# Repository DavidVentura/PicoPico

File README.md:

# Pico Pico

Project to attempt to create hardware for the [Pico-8](https://www.lexaloffle.com/pico-8.php).

I'd like to eventually get full game running on a ~[Raspberry Pi Pico](https://www.raspberrypi.com/documentation/microcontrollers/raspberry-pi-pico.html)~ [ESP32](https://www.adafruit.com/product/3979)

Be aware, the code will be terrible, this is a project to learn:

* C
* SDL
* Embedded
* CMake
* Lua
    * And how to adapt / modify languages
* JIT-ting ??

This project uses [z8lua](https://github.com/DavidVentura/z8lua) to implement Pico8's Lua dialect; I've whacked the original repo to make it build 
with the Pico as a target, it was all implicit casting, which I hopefully got right.

This project also gets some "inspiration" from [tac08](https://github.com/0xcafed00d/tac08/tree/master/src) - ideas for things I don't know how to solve, and the "firmware.lua" file 
for basic implementations.

## Demo

### In emulator (SDL/rawdraw backed)

https://user-images.githubusercontent.com/3650670/209883786-df8e24eb-6469-4147-87f5-97d2407c08f9.mp4

### Celeste in ESP32

https://user-images.githubusercontent.com/3650670/168416377-bf238d62-6be6-4b70-a04c-2d60ab57a269.mp4

### In Raspberry pi Pico (port abandoned, not enough RAM)

https://user-images.githubusercontent.com/3650670/166146124-06b8b223-27b1-47ac-931f-67ba8b523d9e.mp4

### On Android

https://github.com/DavidVentura/PicoPico/assets/3650670/8b1ce7c6-c577-427d-8bed-b0ab688078c9

### On 3DS

https://github.com/DavidVentura/PicoPico/assets/3650670/648f5ae0-5fe0-4eac-8bdf-cbaad8db8e8a

## Hardware

### BOM

* 1x THT Power switch [TME](https://www.tme.eu/nl/en/details/os102011ma1qn1/slide-switches/c-k/) [PDF](https://www.tme.eu/Document/b47a7178f6dd5c46f052ff087f56764e/OS_series_DTE.pdf)
* 8x SMD button [TME](https://www.tme.eu/nl/en/details/evqq2202w/microswitches-tact/panasonic/) [PDF](https://www.tme.eu/Document/7162409d248aba412c7389d402f46025/EVQQ2series.pdf)
* 1x 10k horixontal potentiometer [TME](https://www.tme.eu/nl/en/details/r0141-2-10k/single-turn-tht-trimmers/sr-passives/) [PDF](https://www.tme.eu/Document/48eb4fb11c5e0c9b1cd467745dfbcb98/R0141-2.pdf)
* 8x SMD 10k resistor
* MAX98357 I2S audio amplifier [ALI](https://www.aliexpress.com/item/1005004280540810.html?spm=a2g0o.order_list.order_list_main.11.5b1c18020Z9uMr)
* ESP32 "Wrover" with 4MB PSRAM [Amazon](https://www.amazon.de/gp/product/B07RWHK65X/ref=ppx_yo_dt_b_asin_title_o08_s00?ie=UTF8&psc=1)
* 1.77" SPI ST7735 128x160 Display (128x128 used for game, 16px for UI, 16px padding) [ALI](https://www.aliexpress.com/item/1005003797803015.html?spm=a2g0o.order_list.order_list_main.23.5b1c18020Z9uMr)

# Goals

1. ✅ Make `hello_world` work without regressions )).
    * ~All letters are white~ (lazy palette evaluation was missing a palette indirection (screen vs draw))
1. ✅ Make `rockets` fully playable (without music // complete SFX).
    * ~Points go up too fast~ (`time()` was returning millis)
1. ✅ Create some basic automated testing.
    * Tests are at `tests/`, they run one (or a few) frames and get output.
    * Need to integrate better into the project; exclusive `ifdef` for header selection
1. Make `celeste` fully playable (without music // complete SFX)
    * ~Clouds suddenly appear~ (bad rectfill types, took uint instead of int)
    * Sometimes 2 celestes appear?? mostly on level crossings
1. Make `valdi` fully playable (without music // complete SFX)
    * ~Renders offset when looking to the left~ (wasn't calculating the sprite width accordingly in `spr()`)
    * `fillp` not implemented (background)
    * ~Super slow after a few resets?~ (`gfx_line` was missing a bounds check, overwriting the delay between frames)
1. Make `awake` fully playable (without music // complete SFX)
    * Colors are super glitched, level2 is also glitched

# Basic analysis / feasibility:

Memory requirements:

* Spritesheet, at 128x128 in size = 16KB 
    * Can move to flash
* Fontsheet, at 128x128 in size = 16KB
    * Can move to flash
* Map, at 64x128 = 8 KB
    * Can move to flash
* Flags, at 2x128 = 256B
    * Can move to flash
* Sound effects, 64x84 = 5376B (~5KB)
    * Can move to flash
* Music patterns, 64x6 = 384B
    * Can move to flash
* Front buffer 128x128/2 = 8KB (x/y position -> palette)
* Back buffer 128x128x2 = 32KB (x/y position -> color, at 16bpp)
* HUD buffer 16x128x2 = 4KB
    * Can squeeze to 8x64x2 = 1KB, or even 7 sprites (896b)
* Dedicated "Game memory" = 32KB

Totals ~130KB (of which 76KB for screen buffers and game memory have to stay).

And **most importantly** 2MB for game RAM (Lua memory). This varies based on each game, but on the PICO the 264KB ran out pretty fast. There's [this thing](https://github.com/yocto-8/yocto-8/blob/main/doc/extmem.md) to use _very slow, very cursed_ external RAM. _Some_ games 

# Performance

In RPI Pico:

Running `hello_world.lua`:

* Normal: 13ms / frame; of which:
    * Lua: ~9ms / frame
    * Copying backbuffer to screen (`uint8_t`): ~4ms / frame

* Display on 2nd core: 7.5ms / frame; of which:
    * Lua: ~7ms / frame
    * ~Copying backbuffer to screen~ happens "for free" in the other core

* Multicore + overclock to 260MHz: 3.5ms/frame

In ESP32:

Celeste takes about 9ms / frame (rendering happens on the second core), including SFX

# TODO

Immediate:

* ~Get basic rendering on the Pico~
    * ~split backends properly~
* ~Read code from p8 file instead of having split files~
* ~Implement map~
* ~Implement camera~
* ~Lua dialect~ (using z8lua)
* ~Unify the build systems (Make for pc / CMake for pico)~
* ~Pre-encode the palette colors as a RGB565 `uint16_t`; makes no sense to shift them on _every pixel write_~
* ~SFX~
* ~Measure and output the correct number of samples out of the audio buffer, currently it's a (badly) guessed number.~
* ~Get reasonable audio quality out of SFX~
* Deal with warnings when building for ESP
    * ~Figure out why they don't show up when building with SDL backend~
* ~Move hardcoded pin for ESP32 to sdkconfig~
    * Extract current values for docs WIP
* Implement more complete SFX
* Generate board captures automatically
* ~Add support for short-hand print ('?"x"' == print("x"))~
* Implement fillp https://pico-8.fandom.com/wiki/Fillp
* Lua error: bad argument #1 to 'split' (string expected, got nil)
* Lua error: bad argument #1 to 'btn' (number expected, got nil)
    * z8lua considers literal circle (🅾️) to be `nil` but not ❎

Later:

* ~Clock rate on SPI?~ set to 62.5MHz; not sure if it can go higher
* Implement flash
    * cartdata command could use it
    * carts could be stored in flash instead of static data
* Investigate pushing pixels to display via DMA
    * worth it? the second core is idle anyway
* Music
* Look at optimizing lua bytecode for "fast function calls", for "standard library"
* Use headers instead of stupid ifdefs
* Enable `-Wconversion`
* Console-based UI game
    * [Virtual keyboard](https://www.lexaloffle.com/bbs/?tid=41855) [(original, no lowercase)](https://www.lexaloffle.com/bbs/?tid=4076)
    * Wifi menu
    * Cart explorer?

# Other stuff

Resources are parsed from plaintext into a header by the `to_c.py` script, this also covers converting source code to byte-code. 
Having byte-code compiled in a pre-processing stage makes parsing faster (112ms -> 18ms for a large cart), uses less memory (bytecode 
stays in flash, not necessary to load to RAM) and enables future bytecode-level optimization

## Sound

I yoinked [zepto8's synth](https://github.com/samhocevar/zepto8/blob/master/src/synth.cpp) and converted it to `fix32`; an example SFX went 
from ~25ms to ~2ms on the ESP32.

# API Support

## Graphics

|    Function   | Supported |                     Notes |
|---------------|-----------|---------------------------|
|camera         |✅         |                           |
|circ           |✅         |                           |
|circfill       |✅         |                           |
|oval           |✅         |                           |
|ovalfill       |✅         |                           |
|clip           |✅         |                           |
|cls            |✅         |                           |
|color          |✅         |                           |
|cursor         |❌         |                           |
|fget           |✅         |                           |
|fillp          |❌         |                           |
|fset           |❌         |                           |
|line           |✅         |                           |
|pal            |⚠️          |Only "draw palette" is implemented|
|palt           |✅         |                           |
|pget           |✅         |                           |
|print          |⚠️          |Does not automatically scroll|
|pset           |✅         |                           |
|rect           |✅         |                           |
|rectfill       |✅         |                           |
|sget           |✅         |                           |
|spr            |✅         |                           |
|sset           |✅         |                           |
|sspr           |⚠️          |                           |
|tline          |❌         |                           |

## Tables

All implemented (z8lua)

## Input

`btn` implemented

## Sound

|    Function   | Supported |                     Notes |
|---------------|-----------|---------------------------|
|sfx            |⚠️          | Offset is not implemented |
|music          |❌         |                           |

## Map

All implemented

## Memory

Not implemented

## Math

All implemented (z8lua)

## Cartridge data

|    Function   | Supported |                     Notes |
|---------------|-----------|---------------------------|
|cartdata       |⚠️          | Not persistent            |
|dget           |⚠️          | Not persistent            |
|dset           |⚠️          | Not persistent            |
|cstore         |❌         |                           |
|reload         |❌         |                           |
cartdata/dget/dset are _technically_ implemented, there's no persistence layer though.

cstore/reload are not implemented.

## Coroutines

Implemented by aliasing (z8lua)

## Strings 

Implemented (z8lua)

## Values and objects

Implemented (z8lua)

# Hardware

Build something like the [PicoSystem](https://shop.pimoroni.com/products/picosystem?variant=32369546985555) ?

# Development setup

```bash
sudo apt install cmake g++ libsdl2-dev
git submodule update --init
mkdir pc_pico && cd pc_pico
cmake -DBACKEND=PC ..
```

# Development on RP2040 (without a second Pico running OpenOCD)

Add this block to a udev rule (adjust the paths to point to this repo)
```
SUBSYSTEM=="block", ATTRS{idVendor}=="2e8a", ATTRS{idProduct}=="0003", ACTION=="add", SYMLINK+="rp2040upl%n"
SUBSYSTEM=="block", ATTRS{idVendor}=="2e8a", ATTRS{idProduct}=="0003", ACTION=="add", RUN+="/home/david/git/luatest/udev_build.sh rp2040upl%n"
```

Then having an open minicom shell 
```
sudo minicom -b 115200 -D /dev/ttyACM1
```

you can press `r` on it to reboot into mass-storage mode; which will trigger the udev rules after a second or so.

# Tests

There's a CMake backend (TEST) that you can use with `cmake -DBACKEND=TEST`; in that backend, the command `make test` will run some tests.

Some of the tests are for the internal APIs, and are written in C. Generally though, most tests should be written as p8 cartridges and placed in `tests/regression/*.p8`.

Internal API tests usually compare the output with some expected, known-good frontbuffer values (a "screenshot").
Whenever these need to change, the specific test can be re-run with the environment variable `OVERWRITE_TEST_BUF` set to any value.
This will overwrite `tests/data/buf_*.bin`. To look at these buffers, you can use the command `bin_to_png`.

```
> make test
Running tests...
Test project /Users/tati/git/PicoPico/tests_build
    Start 1: test_hello_world
1/5 Test #1: test_hello_world .................   Passed    0.03 sec
    Start 2: test_hud
2/5 Test #2: test_hud .........................   Passed    0.03 sec
    Start 3: test_menu
3/5 Test #3: test_menu ........................   Passed    0.03 sec
    Start 4: test_primitives
4/5 Test #4: test_primitives ..................   Passed    0.03 sec
    Start 5: test_regression
5/5 Test #5: test_regression ..................   Passed    0.03 sec

100% tests passed, 0 tests failed out of 5

Total Test time (real) =   0.16 sec
```

```
> ./test_regression
Testing regression_api_p8
  test_map_no_args                        [ OK]
  test_print_p8scii_color                 [ OK]

Testing regression_asan_p8
  test_sspr_same_size_is_maintained       [ OK]
  test_circ_top_left_edge                 [ OK]

Testing regression_other_p8
  test_nothing                            [ OK]
```

# Useful links

* [Easy intro to Embedding lua](https://lucasklassmann.com/blog/2019-02-02-how-to-embeddeding-lua-in-c/#example-of-error-handling)
* [Lua 5.2 Manual](https://www.lua.org/manual/5.2/manual.html)
* [Storing data in flash](https://kevinboone.me/picoflash.html?i=1)
* [Udev rule to copy build automatically](https://forums.raspberrypi.com/viewtopic.php?t=333160)
* [Getting started on basic Pico8 Gamedev](https://lukemerrett.com/getting-started-with-pico-8/)
* [GameTiger, another Pico-based console](https://github.com/codetiger/GameTiger-Console)
* [Espressif docs](https://docs.espressif.com/projects/esp-idf/en/latest/esp32/get-started/linux-macos-setup.html)
* [Importing custom 3D models into kicad](https://happyrobotlabs.com/posts/tutorials/tutorial-3d-kicad-parts-using-openscad-and-wings3d/)

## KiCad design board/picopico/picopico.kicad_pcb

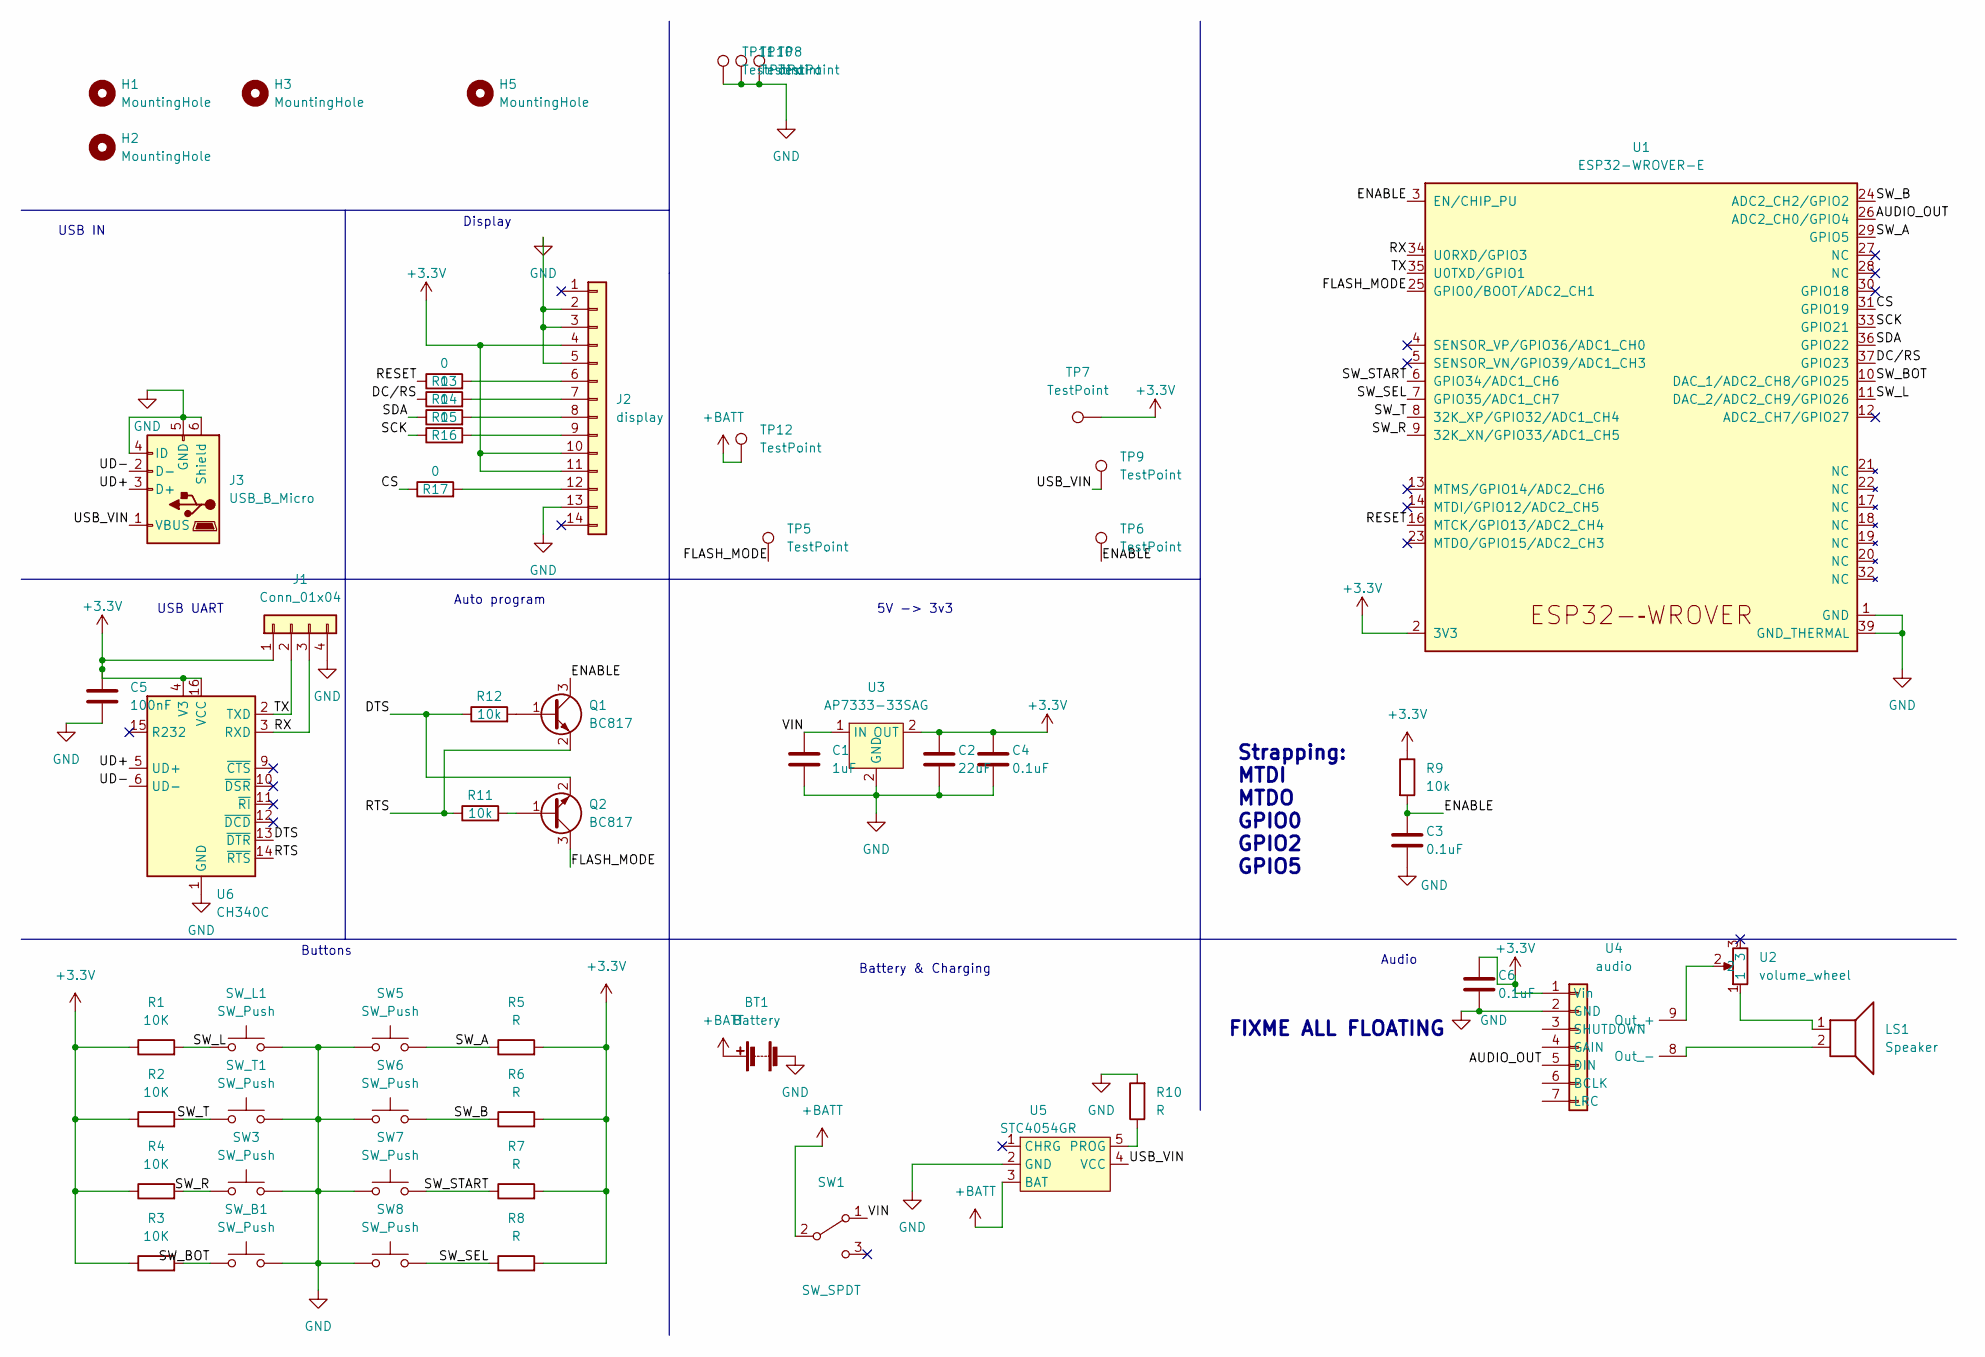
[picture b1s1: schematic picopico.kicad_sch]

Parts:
BT1: Battery; SM02B-SRSS-TB
C1: 1uF; C_1206_3216Metric
C2: 22uF; C_1206_3216Metric
C3, C4, C6: 0.1uF; C_1206_3216Metric
C5: 100nF; C_1206_3216Metric
H1, H2, H3, H5: MountingHole; MountingHole_2.2mm_M2
J1: Conn_01x04; PinHeader_1x04_P2.54mm_Vertical_SMD_Pin1Right
J2: display; lcd smd
J3: USB_B_Micro; USB_Micro-B_Amphenol_10103594-0001LF_Horizontal
LS1: Speaker; speaker
Q1, Q2: BC817; SOT-23
R1, R2, R3, R4: 10K; R_1206_3216Metric_Pad1.30x1.75mm_HandSolder
R5, R6, R7, R8, R10: R; R_1206_3216Metric_Pad1.30x1.75mm_HandSolder
R9, R11, R12: 10k; R_1206_3216Metric_Pad1.30x1.75mm_HandSolder
R13, R14, R15, R16, R17: 0; R_0201_0603Metric
SW1: SW_SPDT; switch_slide_OS102011MA1QN1
SW3, SW5, SW6: SW_Push; evqq2_compact
SW7, SW8: SW_Push; SW_SPST_B3U-1100P-B
SW_B1: SW_Push; evqq2_compact
SW_L1: SW_Push; evqq2_compact
SW_T1: SW_Push; evqq2_compact
TP5, TP6, TP7, TP8, TP9, TP10, TP11, TP12: TestPoint; pad
U1: ESP32-WROVER-E; ESP32-WROVER-E_ThermalVias
U2: volume_wheel; volume wheel
U3: AP7333-33SAG; SOT-23
U4: audio
U5: STC4054GR; SOT-23-5
U6: CH340C; SOIC-16_3.9x9.9mm_P1.27mm

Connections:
+BATT: BT1.1 (+), SW1.2 (B), TP12.1, U5.3 (BAT)
/AUDIO_OUT: U1.26 (ADC2_CH0/GPIO4), U4.5 (DIN)
/CS: R17.1, U1.31 (GPIO19)
/DC/RS: R14.1, U1.37 (GPIO23)
/DTS: Q2.2 (E), R12.1, U6.13 (~DTR)
/ENABLE: C3.1, Q1.3 (C), R9.2, TP6.1, U1.3 (EN/CHIP_PU)
/FLASH_MODE: Q2.3 (C), TP5.1, U1.25 (GPIO0/BOOT/ADC2_CH1)
/RESET: R13.1, U1.16 (MTCK/GPIO13/ADC2_CH4)
/RTS: Q1.2 (E), R11.1, U6.14 (~RTS)
/RX: J1.3, U1.34 (U0RXD/GPIO3), U6.3 (RXD)
/SCK: R16.1, U1.33 (GPIO21)
/SDA: R15.1, U1.36 (GPIO22)
/SW_A: R5.1, SW5.2, U1.29 (GPIO5)
/SW_B: R6.1, SW6.2, U1.24 (ADC2_CH2/GPIO2)
/SW_BOT: R3.2, SW_B1.1, U1.10 (DAC_1/ADC2_CH8/GPIO25)
/SW_L: R1.2, SW_L1.1, U1.11 (DAC_2/ADC2_CH9/GPIO26)
/SW_R: R4.2, SW3.1, U1.9 (32K_XN/GPIO33/ADC1_CH5)
/SW_SEL: R8.1, SW8.2, U1.7 (GPIO35/ADC1_CH7)
/SW_START: R7.1, SW7.2, U1.6 (GPIO34/ADC1_CH6)
/SW_T: R2.2, SW_T1.1, U1.8 (32K_XP/GPIO32/ADC1_CH4)
/TX: J1.2, U1.35 (U0TXD/GPIO1), U6.2 (TXD)
/UD+: J3.3 (D+), U6.5 (UD+)
/UD-: J3.2 (D-), U6.6 (UD-)
/USB_VIN: J3.1 (VBUS), TP9.1, U5.4 (VCC)
/VIN: C1.1, SW1.1 (A), U3.1 (IN)
unnamed: J2.6, R13.2
unnamed: J2.7, R14.2
unnamed: J2.8, R15.2
unnamed: J2.9, R16.2
unnamed: J2.12, R17.2
unnamed: LS1.1, U2.1
unnamed: LS1.2, U4.8 (Out_-)
unnamed: Q1.1 (B), R12.2
unnamed: Q2.1 (B), R11.2
unnamed: R10.1, U5.5 (PROG)
unnamed: U2.2, U4.9 (Out_+)

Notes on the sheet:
Audio
Auto program
USB UART
Buttons
Display
USB IN
Battery & Charging
Strapping: MTDI MTDO GPIO0 GPIO2 GPIO5
5V -> 3v3
FIXME ALL FLOATING

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
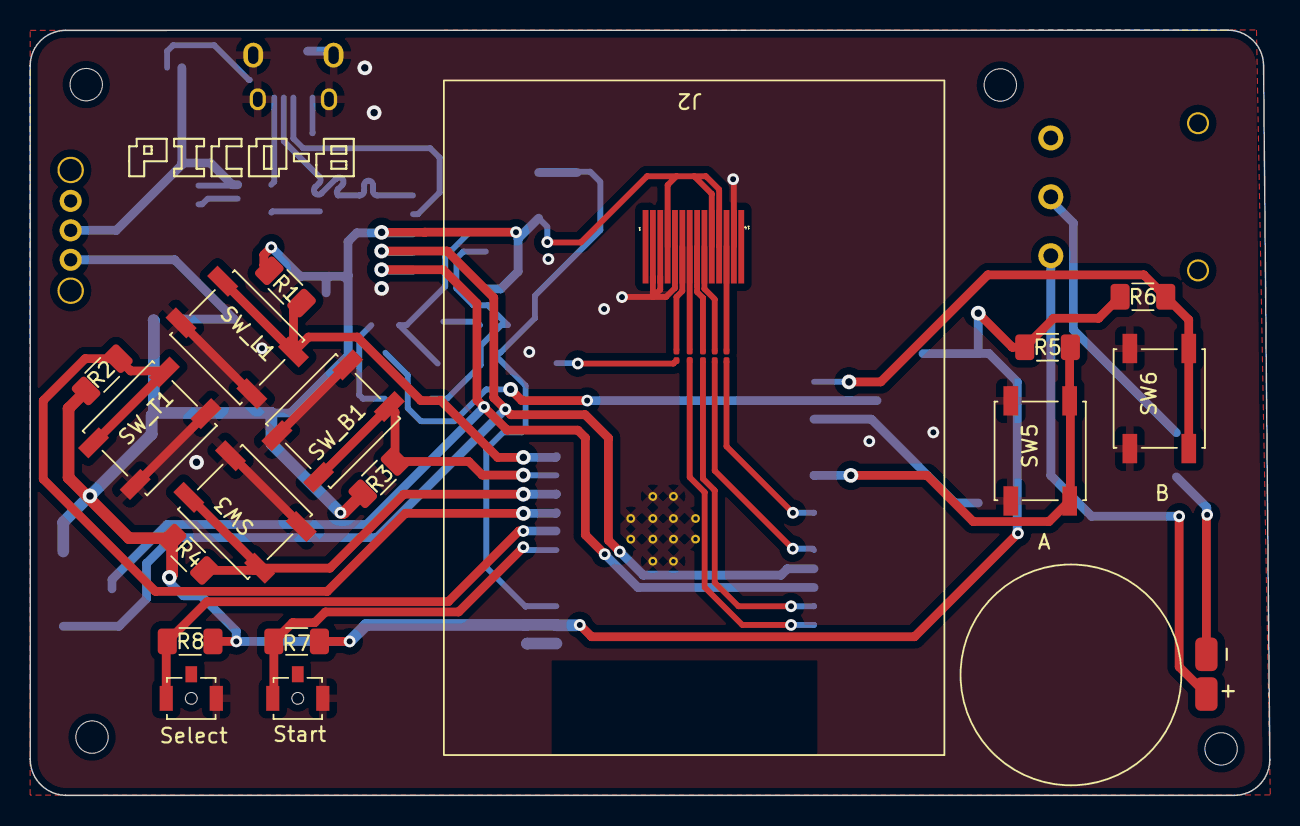
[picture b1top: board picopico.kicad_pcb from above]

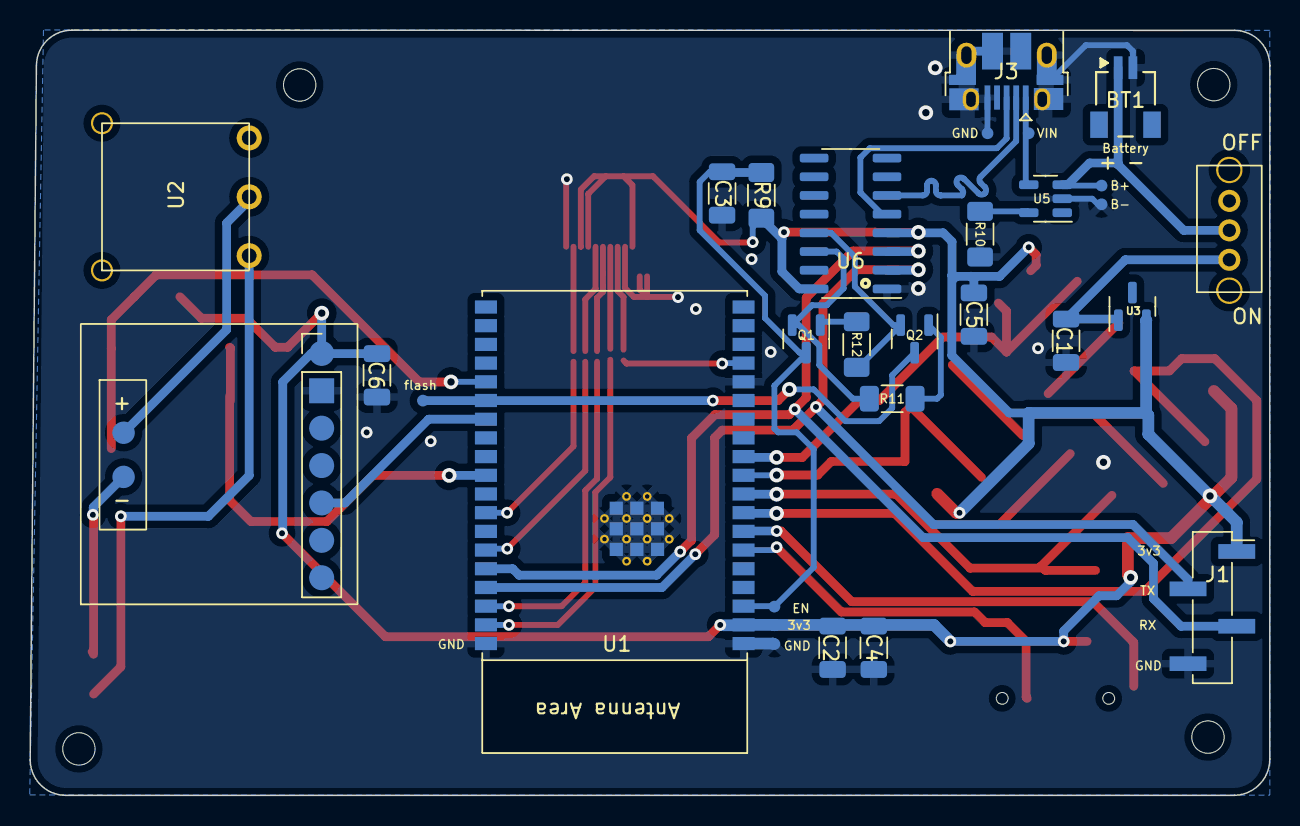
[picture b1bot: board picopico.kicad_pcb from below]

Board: 2 copper layers, 84.2 x 52.0 mm, 57 parts (30 on the bottom side), 38 nets.

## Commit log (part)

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2022-05-05 better bounds checking
2022-05-05 allow pset to take negative values
2022-05-05 trigger a GC step per frame
2022-05-05 move some debug lines
2022-05-06 notes
2022-05-06 use new st7789 display
2022-05-06 move main functions to engine
2022-05-06 implement flag parser
2022-05-06 update circlefill signature to be 2bytes
2022-05-07 esp hello world building
2022-05-08 re-enable gfx_*
2022-05-08 fix gfx_rect* taking width instead of endpos
2022-05-08 push boolean correctly for bitfield
2022-05-08 kinda fix Lua build
2022-05-08 add spiram note
2022-05-08 add notes on ESP32, memory and jit
2022-05-08 add X flip support
2022-05-08 update putpixel and signature on gfx_rect
2022-05-08 remove superfluous printh
2022-05-09 update gfx_*
2022-05-09 blank entire display
2022-05-09 slightly optimize settings
2022-05-09 add headers
2022-05-09 break main so it works on esp
2022-05-09 add table with support
2022-05-09 add notes
2022-05-11 add st7735 drivers
2022-05-11 add -g3 for pc build
2022-05-11 add note on palette optimization
2022-05-11 use ili driver
2022-05-11 unify generic backends
2022-05-11 fix build so all platforms can build at the same time
2022-05-11 use pre-encoded 16-bit rgb565 colors
2022-05-11 placebo perf improvements
2022-05-12 adjust for new display
2022-05-12 add basic sound (that does nothing)
2022-05-12 steal synth from zepto8; get demo of celeste jump sfx
2022-05-13 optimizations
2022-05-13 user proper len for buf
2022-05-13 convert to fixed point math (only triangle wave)
2022-05-14 implement SFX
2022-05-14 convert other instruments to f32
2022-05-14 implement sfx offset
2022-05-14 transfer audio via a task using dma
2022-05-14 rename speed to duration
2022-05-14 re-organize audio to fill buffers on callback; similar to how the DMA requests are executed on ESP32
2022-05-14 set up audio with dma for esp
2022-05-15 add notes on SFX dma
2022-05-15 Fix buffer overflow on audio
    Shouldn't add the whole `SAMPLES_PER_DURATION` -- each iteration adds an
    extra "1" to this count; so should add `SAMPLES_PER_DURATION-1` instead
2022-05-15 store sfx_id
2022-05-15 implement stat partially; expose _circ
2022-05-15 call _init before checking for existence of _draw and _update
2022-05-15 use pen-color for default colors
2022-05-15 alias t to time
2022-05-15 tolerate null SFX id
2022-05-15 implement mset and clip
2022-05-15 implement palette replacement via table on pal()
2022-05-15 cap rect/rectfill at screen
2022-05-15 implement color()
2022-05-15 allow drawing multiple sprites in one go (spr support for w/h)
2022-05-15 do not draw sprite #0 on map()
2022-05-15 slightly optimize circlefill
2022-05-15 put both secondary tasks on core #1
2022-05-15 fix fget calculation
2022-05-15 stop sfx on id -1
2022-05-16 enforce usage of single precision floats
2022-05-16 yoink apply_fx
2022-05-16 bump to lua without doubles
2022-05-18 add notes on optimization for lua
2022-05-18 bump lua
2022-05-18 update log
2022-05-18 notes on extra optimizations
2022-05-20 more notes on optimization
2022-05-21 remove foreach from stdlib
2022-05-21 use fix32 instead of float
2022-05-21 use ms for timestamp
2022-05-21 call optimized fast_render when theres no flip/stretch
2022-05-21 update rockets example
2022-05-21 update pc cmake rules
2022-05-21 notes on fixed point calc for sin/cos
2022-05-22 do not paint transparent pixels
2022-05-22 fix x/y max calculation
2022-05-28 use external i2s chip
2022-05-30 audio debug
2022-05-30 start refactoring for AOT lua
2022-05-30 adjust esp backend for I2S chip
2022-05-30 add id on sfx
2022-05-30 add spi_flash to requires
2022-06-06 split print so it can be called directly from AOT
2022-06-06 cleanup
2022-06-06 expose `spr` and `btn` to AOT
2022-06-07 remove broken optimization from _render
2022-06-07 cast as float
2022-06-13 update sdkconfig
2022-09-18 dump
2022-09-18 bump
2022-09-18 add instructions for setup
2022-10-02 add hud placeholder
2022-10-02 add board
2022-10-02 add hw details
2022-10-03 update sdk
2022-10-03 comment out decl
2022-10-15 board stuff
2022-10-15 add hud
2022-10-15 add hud stuff
2022-10-15 Revert "update sdk"
    This reverts commit 3a7c0a7248e9e47df38a72b0bb6d1e7b8050b992.
2022-10-16 add board stuff
2022-10-16 update board
2022-10-19 board update
2022-12-17 aot+hud ??
2022-12-26 make all games available on startup
2022-12-26 move data to be used by esp
2022-12-26 improve measurement times
2022-12-27 remove delays for faster boot (1280ms->485ms)
2022-12-27 implement/fix HUD
2022-12-27 format
2022-12-27 remove dead code
2022-12-27 add notes on lua
2022-12-28 remove parsing from code
2022-12-28 add trailing null byte
2022-12-28 Make luac emit 32-bit bytecode
2022-12-28 load bytecode directly
2022-12-28 add notes on resources
2022-12-28 implement bottommost 32 map tiles
2022-12-28 better handling of menu transition
2022-12-28 always use bytecode
2022-12-28 flush prints
2022-12-28 add label and display it in menu
2022-12-28 small cleanup
2022-12-28 nicer game pick screen
2022-12-28 make Channel offset uint32_t
2022-12-28 split hud to file
2022-12-28 split sfx to file
2022-12-28 split code into engine/api/backend
2022-12-28 compile stdlib
2022-12-28 remove cart instance
2022-12-28 update readme notes
2022-12-28 add platform init
2022-12-28 actually refresh the hud
2022-12-29 fix resource generation target
2022-12-29 add cppcheck target
2022-12-29 update for new warnings
2022-12-29 implement render_text to render text
2022-12-29 add note on shorthand print
2022-12-29 implement poke
2022-12-29 implement flip; refactor code to be flip-based
2022-12-29 update notes
2022-12-29 implement btnp, use btnp in menu
2022-12-29 add mostly-working valdi example
2022-12-30 implement btn with bitfield
2022-12-30 handle negative maps
2022-12-30 add examples
2022-12-31 start converting frontbuffer format
2022-12-31 ovalfill reload wip
2022-12-31 Use packed frontbuffer
2022-12-31 mget should ignore negative values
2022-12-31 fix line conditions
2022-12-31 add goals
2022-12-31 update rockets
2022-12-31 add poke4
2022-12-31 return time in seconds
2022-12-31 remove duplicate sleep
2022-12-31 fix width calculation on spr()
2022-12-31 save altered palette states in frontbuffer
2022-12-31 run lua_gc passes per frame
2022-12-31 Fix rectfill
2022-12-31 Add bounds check on gfx_line
    Was overwriting `frame_end_time`, making some sleeps randomly take very
    long
2022-12-31 remove more parsing
2022-12-31 add basic testing
2022-12-31 add tests, broken hello-world
2022-12-31 update pointer size
2023-01-01 add warning on overwriting tests; fix test file mode; update helloworld test
2023-01-01 add warning on overwriting tests
    update helloworld test, was overwriting results every time
2023-01-01 bugfixes for esp32 from refactoring
2023-01-01 style
2023-01-01 move hardcoded pin settings to kconfig
2023-01-02 Add netlist vs kconfig checking tool
2023-01-02 fix tool
2023-02-05 rewire board
2023-02-12 board
2023-02-19 gitignore
2023-02-19 add switch model
2023-02-19 remove cache files
2023-02-22 add selection for builting DAC or external I2S one
2023-02-26 add board v2
2023-02-26 add version with antenna on top
2023-02-27 move esp down
2023-03-01 more board changes
2023-03-03 more board stuff
2023-03-04 add sm02b
2023-03-04 add board graphics
2023-03-05 misc
    * add update60 support
    * add srand support
    * add extcmd stub
2023-03-05 add some crashy examples
2023-03-05 fix fps detect
2023-03-05 btnp with no args
2023-03-05 fix signature for spr() taking uint16_t
2023-03-11 bail from map() if no arguments are passed
2023-03-11 use guarded_put_pixel for circles
2023-03-11 add lua regression tests
2023-03-11 better handling of failing tests
2023-03-11 fix menu test
2023-03-12 improve regression tests
2023-03-12 parse cart before testing
2023-03-12 maintain sspr size instead of hardcoding 8
2023-03-12 split tests
2023-03-12 observe camera x/y on print
2023-03-12 more accurecate circfill
2023-03-12 implement \f in print for fg color
2023-03-12 print special wide and tall chars
2023-03-12 add support for printing arrows
2023-03-12 support background colors on print
2023-03-12 bg color for text
2023-03-12 tolerate bigger circfills
2023-03-12 fix rect & fewer wraparounds
2023-03-12 fix sprite flip
2023-03-12 make circle safe again
2023-03-13 support \n and better bg color for print
2023-03-13 fix bg color on print
2023-03-13 implement ^g ^-
2023-03-13 stop badcasting to int8
2023-03-14 fix guarded
2023-03-14 bump with ? rules
2023-03-14 fix oval
2023-03-14 improve tests; add primitives test
2023-03-14 implement cursor()
2023-03-14 fix spritesheet bounds check
2023-03-15 implement sset
2023-03-15 make line observe camera
2023-03-15 mset
2023-04-06 read env var to overwrite buf
2023-04-06 split out cart_index
2023-04-06 small clean
2023-04-06 bail on wrong backends
2023-04-06 add http server to look at test output
2023-04-07 point to new version
2023-04-07 bounds checking on pget
2023-04-07 upper bound check
2023-04-07 bounds checking on map cells
2023-04-12 implement print for heart font
2023-04-12 add codesign on macos
2023-04-17 blah
2023-05-18 add datasheets
2023-05-18 enable start/select buttons
2023-05-18 update gpios & bump ESP32_REV_MIN
2023-05-22 add rawdraw
2023-05-23 add stuff for rawdraw
2023-05-23 mostly handle input; fix now() calculation
2023-05-24 implement good multitouch support
2023-05-24 add some circle ui
2023-05-26 add 3ds backend, works in emulator
2023-05-26 scale, handle input
2023-05-27 allow scaling factor & create rendering thread
2023-05-27 remove threads, crash on console
2023-05-27 update lua
2023-05-27 use OGL on pc
2023-05-27 gate input behind android flag; free texture on exit
2023-05-27 better split of android vs pc
2023-05-27 add extra examples
2023-05-27 maybe working cmake android
2023-05-28 faster builds; set dependencies properly
2023-05-28 add Nintendo 3DS backend
2023-05-28 add script to build all targets
2023-05-28 draw labels with instructions on bottom
2023-05-28 small cleanup and remove debug from 3ds
2023-05-28 add workflow
2023-05-28 quote
2023-05-28 trigger build
2023-05-28 fix-branch
2023-05-28 image
2023-05-28 recursive
2023-05-28 add git to img
2023-05-28 nossl
2023-05-28 update-with-python
2023-05-28 compile a luac for x86 big sad
2023-05-28 fix build
2023-05-28 built in container
2023-05-28 maybe build lua this time
2023-05-28 use default icon
2023-05-28 specify android sdk path
2023-05-28 upload artifacts individually
2023-05-28 constant for button indices
2023-05-28 refactor
2023-05-28 more cleanup
2023-05-28 refactor more
2023-05-28 Refactor (#5)
2023-05-28 oops
2023-05-28 play audio in rawdraw mode
2023-05-28 add alsa libs
2023-05-28 bump to use alsa libs
2023-05-29 Add audio on android
2023-05-29 Update submodule
2023-05-29 handle android suspend a bit better
2023-05-29 some weir stuff for wasm
2023-05-29 wip audio
2023-05-29 working sinewave mono
2023-05-29 working audio on 3ds
2023-05-30 refactor a bit
2023-05-30 add test cov
2023-05-30 add gcovr
2023-05-30 2bpp bufsize
2023-06-01 update paths
2023-06-05 make work with esp32
2023-06-05 add boardv2 stuff
2023-06-25 break everything to move to custom-lua
2023-06-30 big refactor, kinda works
2023-06-30 load games based on cart name
2023-06-30 re-enable circ/rect/oval/line
2023-07-01 better resource cleanup
2023-07-01 return bool on btn
2023-07-01 print numbers
2023-07-02 compile to embedded shared objects
2023-07-02 pipe through black
2023-07-02 bump code_len
2023-07-02 remove luac
2023-07-02 load the shared object directly from embedded
2023-07-02 remove stdlib lua
2023-07-02 add bunch of func api declarations
2023-07-03 add all
2023-07-03 call by slice
2023-07-04 use TVSlice_t, move count & rnd
2023-07-05 add more functions
2023-07-06 make foreach generic
2023-07-08 build math and table
2023-07-08 move stuff around, mostly out of here into lua
2023-07-08 some more funcions
2023-07-08 point to new files
2023-07-09 start reimplementing some of the commented out functions
2023-07-10 remove math/table functions
2023-07-10 make print return the next X coordinate
2023-07-10 pass correct files to compiler
2023-09-02 call fast_render when possible
2023-09-02 allow spr to be called with only sprite
2023-09-03 add debug logging for draw/update calls
